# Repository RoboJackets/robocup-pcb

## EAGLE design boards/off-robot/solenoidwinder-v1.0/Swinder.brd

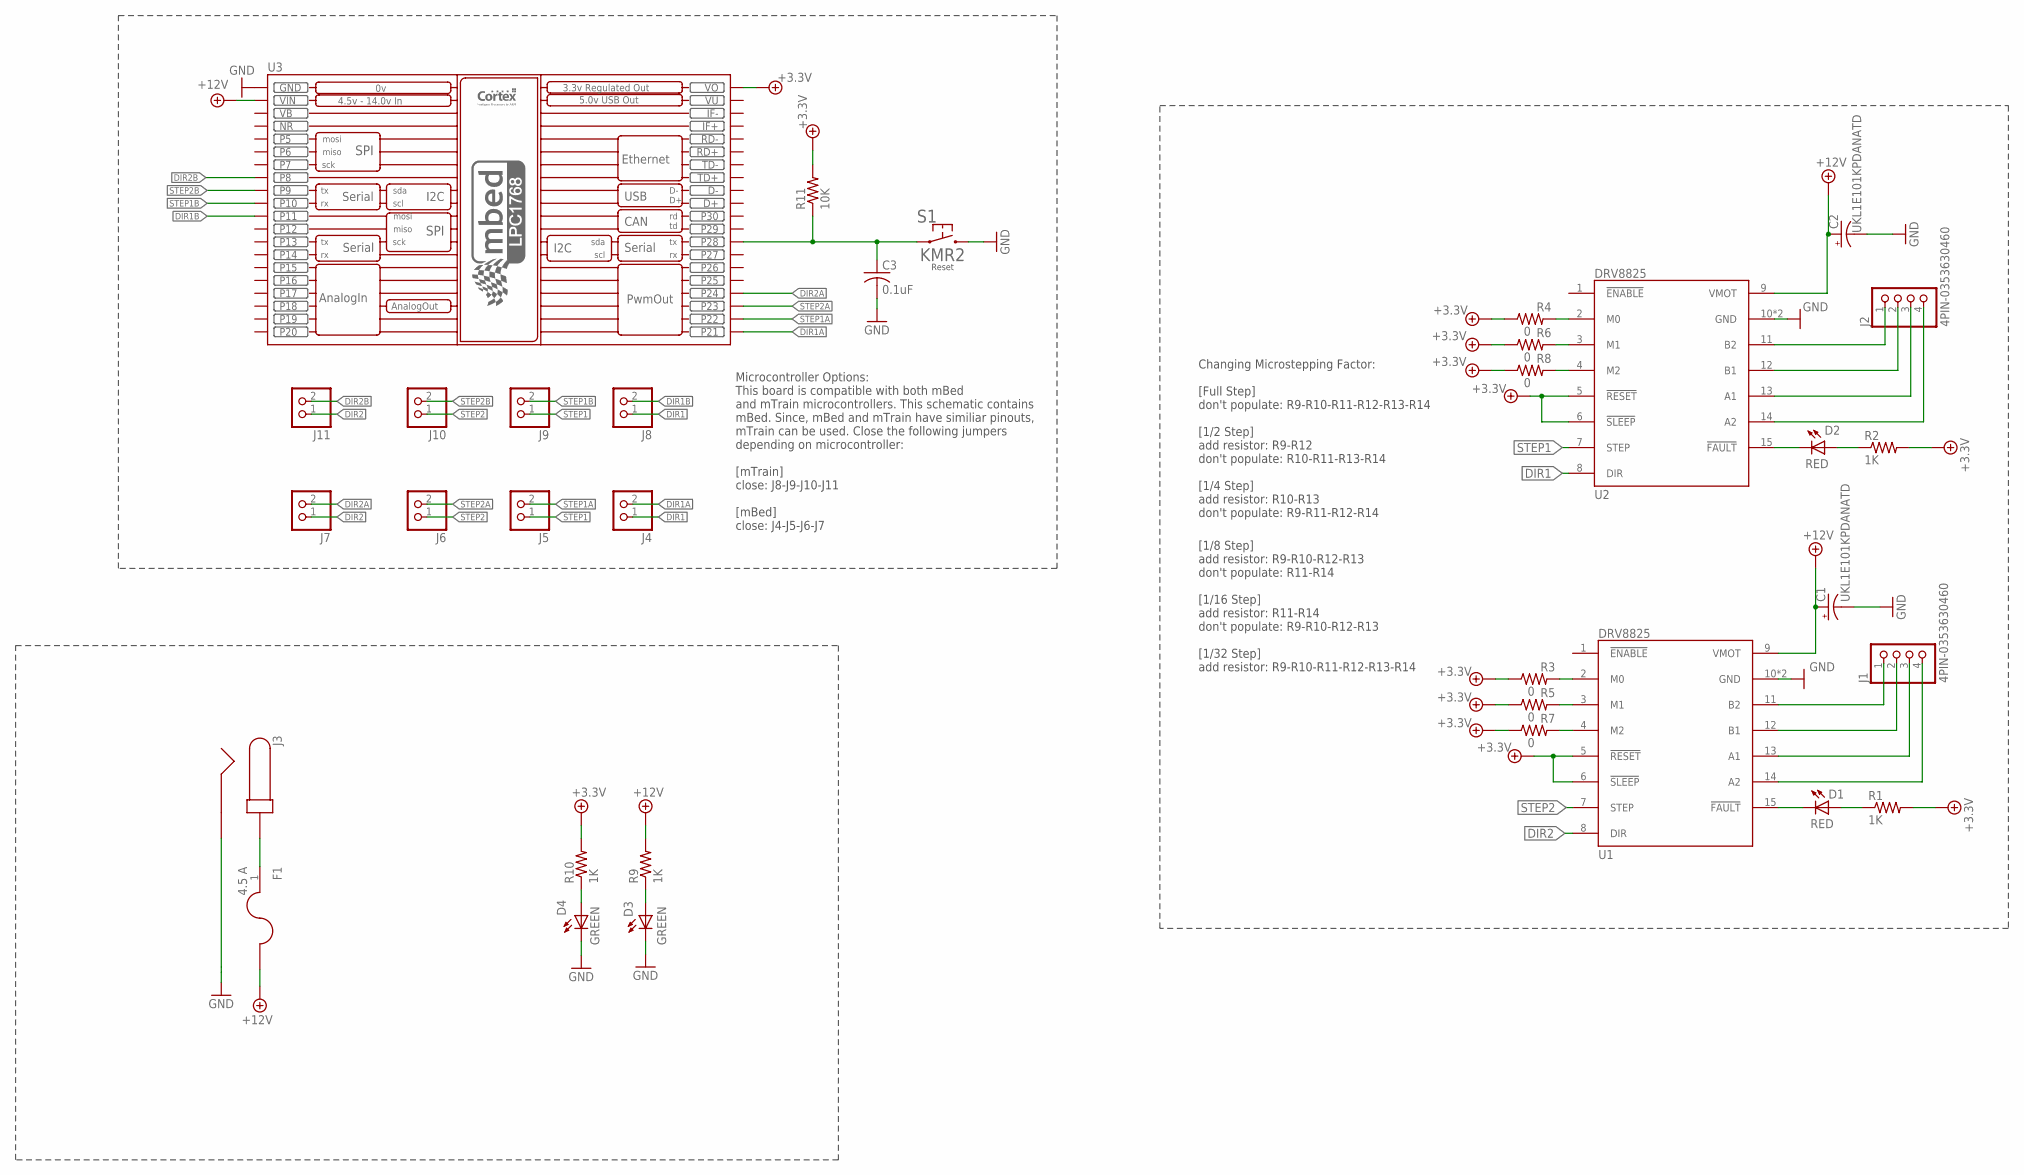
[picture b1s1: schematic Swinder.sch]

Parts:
C1, C2: UKL1E101KPDANATD
C3: 0.1uF; C0603
D1, D2: RED; CHIP-LED0603
D3, D4: GREEN; CHIP-LED0603
F1: 4.5 A; F1206
J1, J2: 4PIN-0353630460; 0353630460
J3: PJ-037A
J4, J5, J6, J7, J8, J9, J10, J11: CONN-2VERT; 1X2
R1, R2, R9, R10: 1K; R0603W
R3, R4, R5, R6, R7, R8: 0; R0603W
R11: 10K; R0603W
S1: KMR2
U1, U2: DRV8825
U3: MBED_NXP_LPC1768; MBED-KIT

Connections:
+3.3V: R1.2 (PIN2), R2.2 (PIN2), R3.1 (PIN1), R4.1 (PIN1), R5.1 (PIN1), R6.1 (PIN1), R7.1 (PIN1), R8.1 (PIN1), R10.2 (PIN2), R11.2 (PIN2), U1.5 (!RESET!), U1.6 (!SLEEP!), U2.5 (!RESET!), U2.6 (!SLEEP!), U3.VOUT (VO)
+12V: C1.+, C2.+, F1.2, R9.2 (PIN2), U1.9 (VMOT), U2.9 (VMOT), U3.VIN
A1$1: J2.3, U2.13 (A1)
A1$2: J1.3, U1.13 (A1)
A2$1: J2.4, U2.14 (A2)
A2$2: J1.4, U1.14 (A2)
B1$1: J2.2, U2.12 (B1)
B1$2: J1.2, U1.12 (B1)
B2$1: J2.1, U2.11 (B2)
B2$2: J1.1, U1.11 (B2)
DIR1: J4.1, J8.1, U2.8 (DIR)
DIR1A: J4.2, U3.P$21 (P21)
DIR1B: J8.2, U3.P$11 (P11)
DIR2: J7.1, J11.1, U1.8 (DIR)
DIR2A: J7.2, U3.P$24 (P24)
DIR2B: J11.2, U3.P$8 (P8)
FPOW: F1.1, J3.P$2 (1)
G1: D3.A, R9.1 (PIN1)
G2: D4.A, R10.1 (PIN1)
GND: C1.-, C2.-, C3.2, D3.C (K), D4.C (K), J3.P$1 (2), S1.2.1 (2), S1.2.2 (2), U1.10 (GND), U1.16 (GND), U2.10 (GND), U2.16 (GND), U3.GND
M0-1: R4.2 (PIN2), U2.2 (M0)
M0-2: R3.2 (PIN2), U1.2 (M0)
M1-1: R6.2 (PIN2), U2.3 (M1)
M1-2: R5.2 (PIN2), U1.3 (M1)
M2-1: R8.2 (PIN2), U2.4 (M2)
M2-2: R7.2 (PIN2), U1.4 (M2)
unnamed: C3.1, R11.1 (PIN1), S1.1.1 (1), S1.1.2 (1), U3.P$28 (P28)
R1-1: D2.A, R2.1 (PIN1)
R1-2: D2.C (K), U2.15 (!FAULT!)
R2-1: D1.A, R1.1 (PIN1)
R2-2: D1.C (K), U1.15 (!FAULT!)
STEP1: J5.1, J9.1, U2.7 (STEP)
STEP1A: J5.2, U3.P$22 (P22)
STEP1B: J9.2, U3.P$10 (P10)
STEP2: J6.1, J10.1, U1.7 (STEP)
STEP2A: J6.2, U3.P$23 (P23)
STEP2B: J10.2, U3.P$9 (P9)
VB: U3.VB
VU: U3.VU

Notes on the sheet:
Changing Microstepping Factor: [Full Step] don't populate: R9-R10-R11-R12-R13-R14 [1/2 Step] add resistor: R9-R12 don't populate: R10-R11-R13-R14 [1/4 Step] add resistor: R10-R13 don't populate: R9-R11-R12-R14
[1/8 Step] add resistor: R9-R10-R12-R13 don't populate: R11-R14 [1/16 Step] add resistor: R11-R14 don't populate: R9-R10-R12-R13 [1/32 Step] add resistor: R9-R10-R11-R12-R13-R14
Microcontroller Options: This board is compatible with both mBed and mTrain microcontrollers. This schematic contains mBed. Since, mBed and mTrain have similiar pinouts, mTrain can be used. Close the following jumpers depending on microcontroller: [mTrain] close: J8-J9-J10-J11 [mBed] close: J4-J5-J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

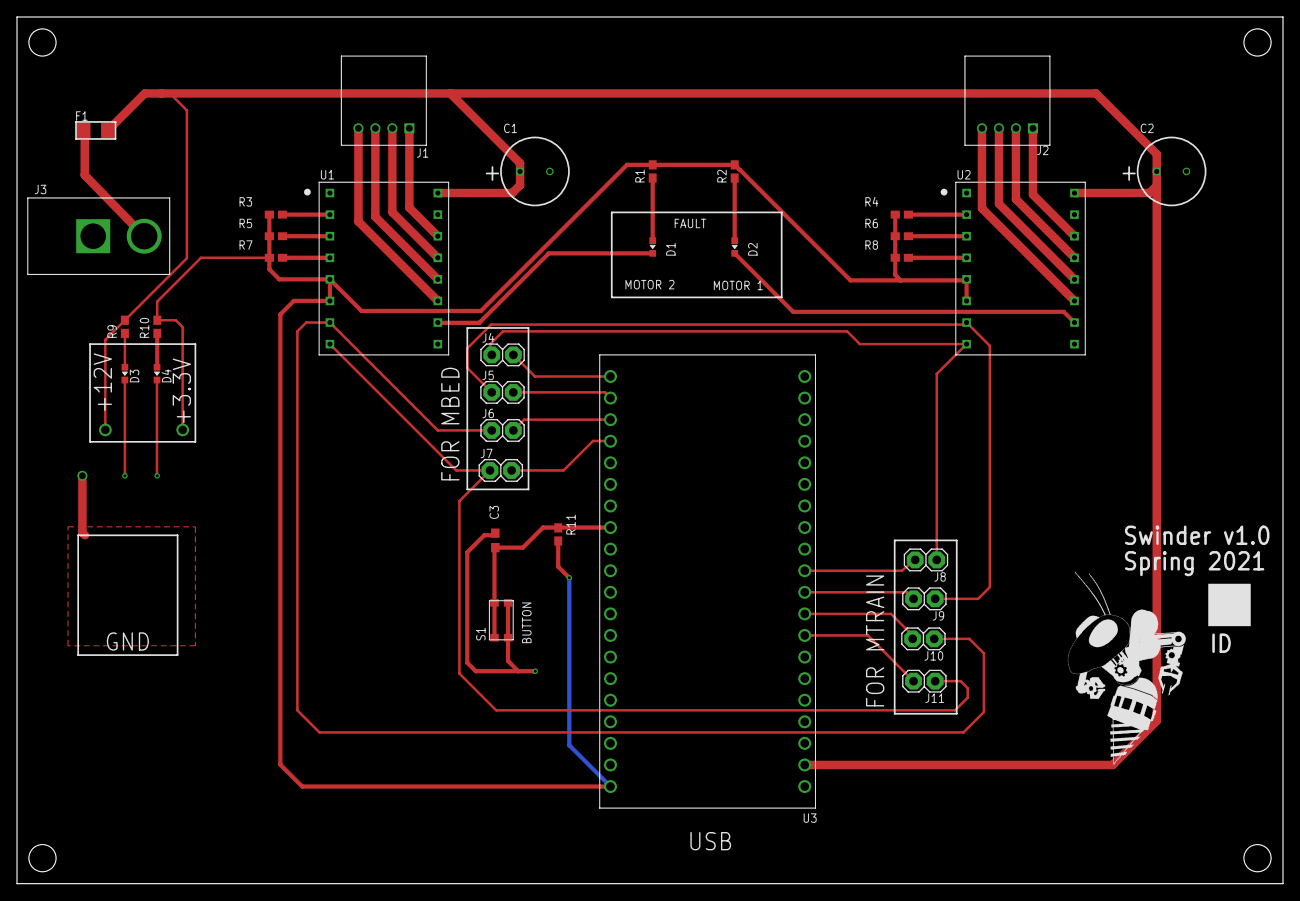
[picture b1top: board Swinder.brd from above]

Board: 2 copper layers, 149.0 x 102.0 mm, 35 parts (0 on the bottom side), 37 nets.

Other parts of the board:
U$1: ROBOBUZZ_1.2X

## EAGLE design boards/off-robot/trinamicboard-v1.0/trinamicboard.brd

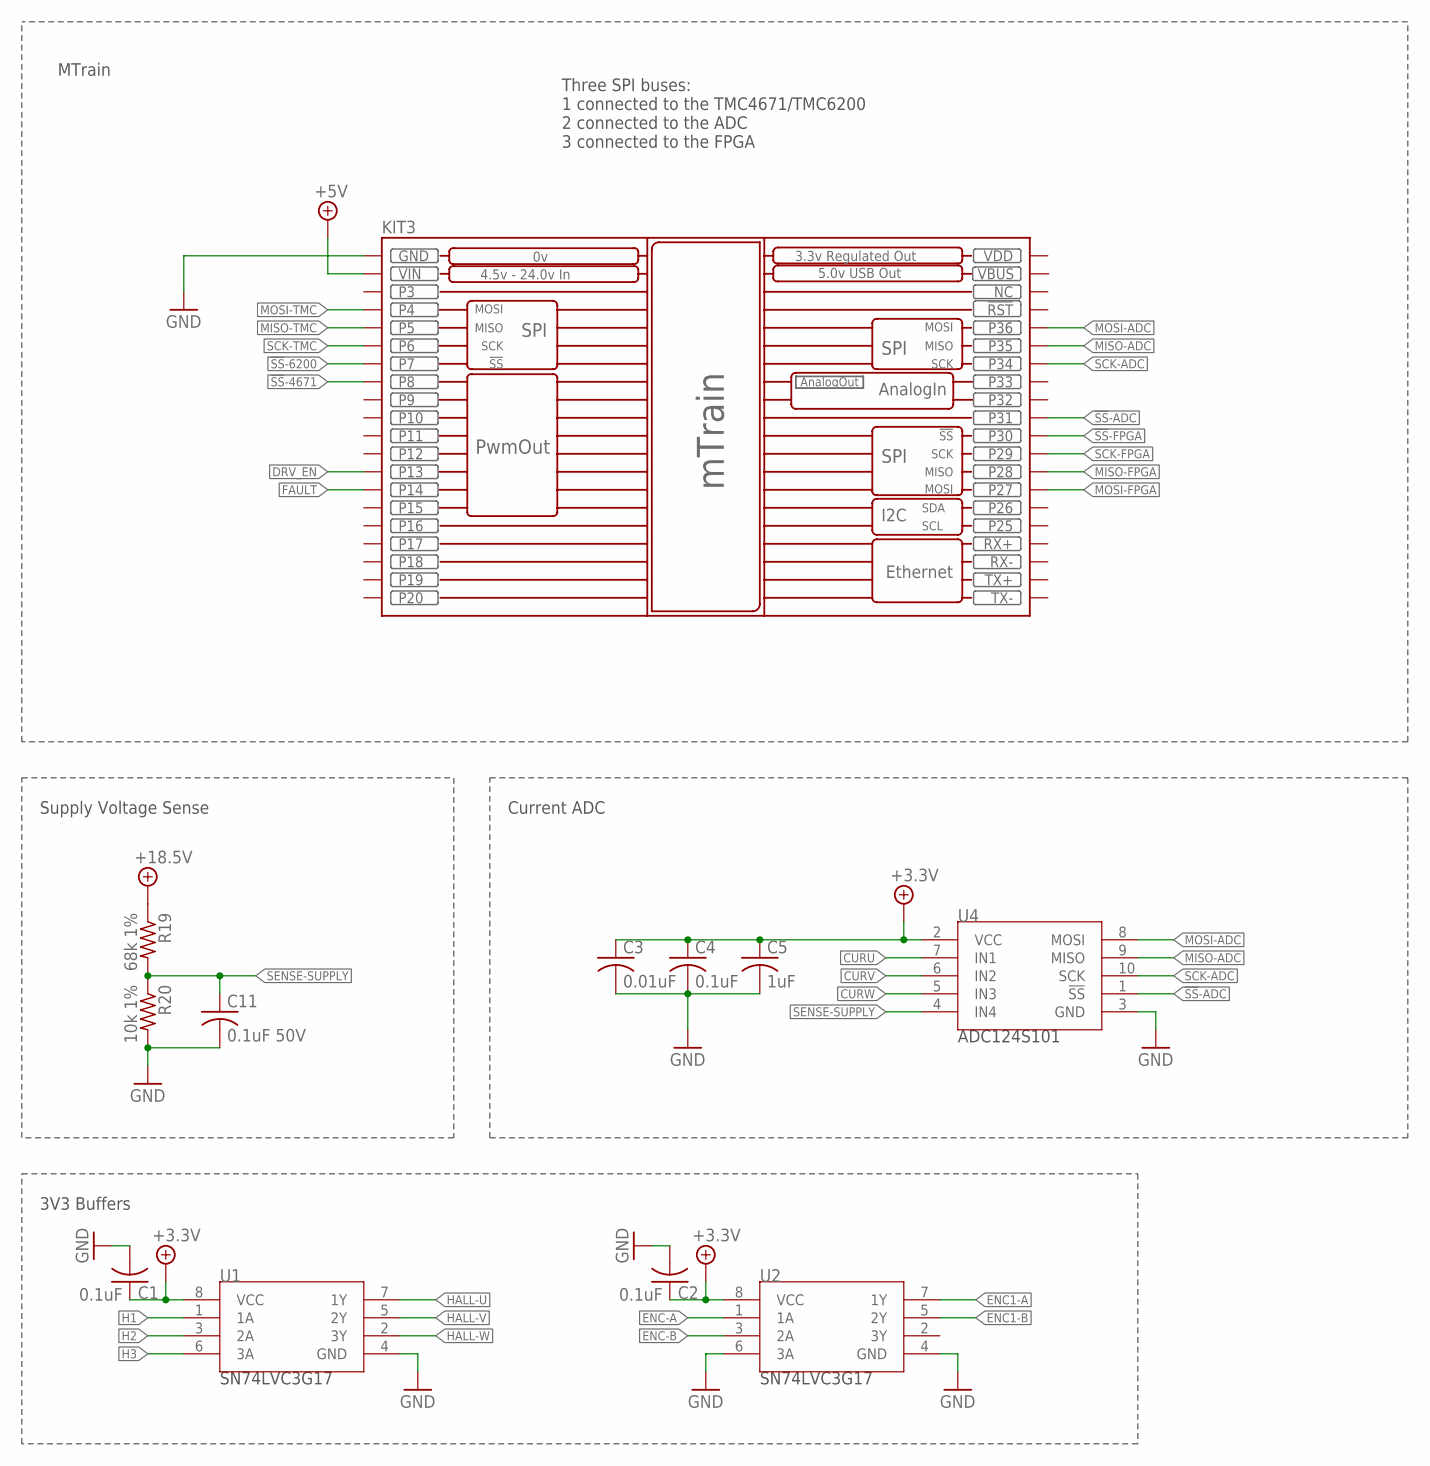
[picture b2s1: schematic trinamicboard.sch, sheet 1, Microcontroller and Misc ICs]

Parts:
C1, C2, C4: 0.1uF; C0603
C3: 0.01uF; C0603
C5: 1uF; C0603
C11: 0.1uF 50V; C0603
KIT3: MTRAIN; MTRAIN-KIT
R19: 68k 1%; R0603
R20: 10k 1%; R0603
U1, U2: SN74LVC3G17; VSSOP-8
U4: ADC124S101; VSSOP-10

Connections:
!SS!-4671: KIT3.P$8 (P8); also elsewhere on the board
!SS!-6200: KIT3.P$7 (P7); also elsewhere on the board
!SS!-ADC: KIT3.P$31 (P31), U4.1 (!SS); also elsewhere on the board
!SS!-FPGA: KIT3.P$30 (P30); also elsewhere on the board
+3.3V: C1.1, C2.1, C3.1, C4.1, C5.1, U1.8 (VCC), U2.8 (VCC), U4.2 (VCC); also elsewhere on the board
+5V: KIT3.VIN; also elsewhere on the board
+18.5V: R19.1; also elsewhere on the board
CURU: U4.7 (IN1); also elsewhere on the board
CURV: U4.6 (IN2); also elsewhere on the board
CURW: U4.5 (IN3); also elsewhere on the board
DRV_EN: KIT3.P$13 (P13); also elsewhere on the board
ENC1-A: U2.7 (1Y); also elsewhere on the board
ENC1-B: U2.5 (2Y); also elsewhere on the board
ENC-A: U2.1 (1A); also elsewhere on the board
ENC-B: U2.3 (2A); also elsewhere on the board
FAULT: KIT3.P$14 (P14); also elsewhere on the board
GND: C1.2, C2.2, C3.2, C4.2, C5.2, C11.2, KIT3.GND, R20.2, U1.4 (GND), U2.4 (GND), U2.6 (3A), U4.3 (GND); also elsewhere on the board
H1: U1.1 (1A); also elsewhere on the board
H2: U1.3 (2A); also elsewhere on the board
H3: U1.6 (3A); also elsewhere on the board
HALL-U: U1.7 (1Y); also elsewhere on the board
HALL-V: U1.5 (2Y); also elsewhere on the board
HALL-W: U1.2 (3Y); also elsewhere on the board
MISO-ADC: KIT3.P$35 (P35), U4.9 (MISO); also elsewhere on the board
MISO-FPGA: KIT3.P$28 (P28); also elsewhere on the board
MISO-TMC: KIT3.P$5 (P5); also elsewhere on the board
MOSI-ADC: KIT3.P$36 (P36), U4.8 (MOSI); also elsewhere on the board
MOSI-FPGA: KIT3.P$27 (P27); also elsewhere on the board
MOSI-TMC: KIT3.P$4 (P4); also elsewhere on the board
SCK-ADC: KIT3.P$34 (P34), U4.10 (SCK); also elsewhere on the board
SCK-FPGA: KIT3.P$29 (P29); also elsewhere on the board
SCK-TMC: KIT3.P$6 (P6); also elsewhere on the board
SENSE-SUPPLY: C11.1, R19.2, R20.1, U4.4 (IN4)
VBUS: KIT3.VBUS
VDD: KIT3.VDD

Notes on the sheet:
MTrain
Supply Voltage Sense
Three SPI buses: 1 connected to the TMC4671/TMC6200 2 connected to the ADC 3 connected to the FPGA
Current ADC
3V3 Buffers

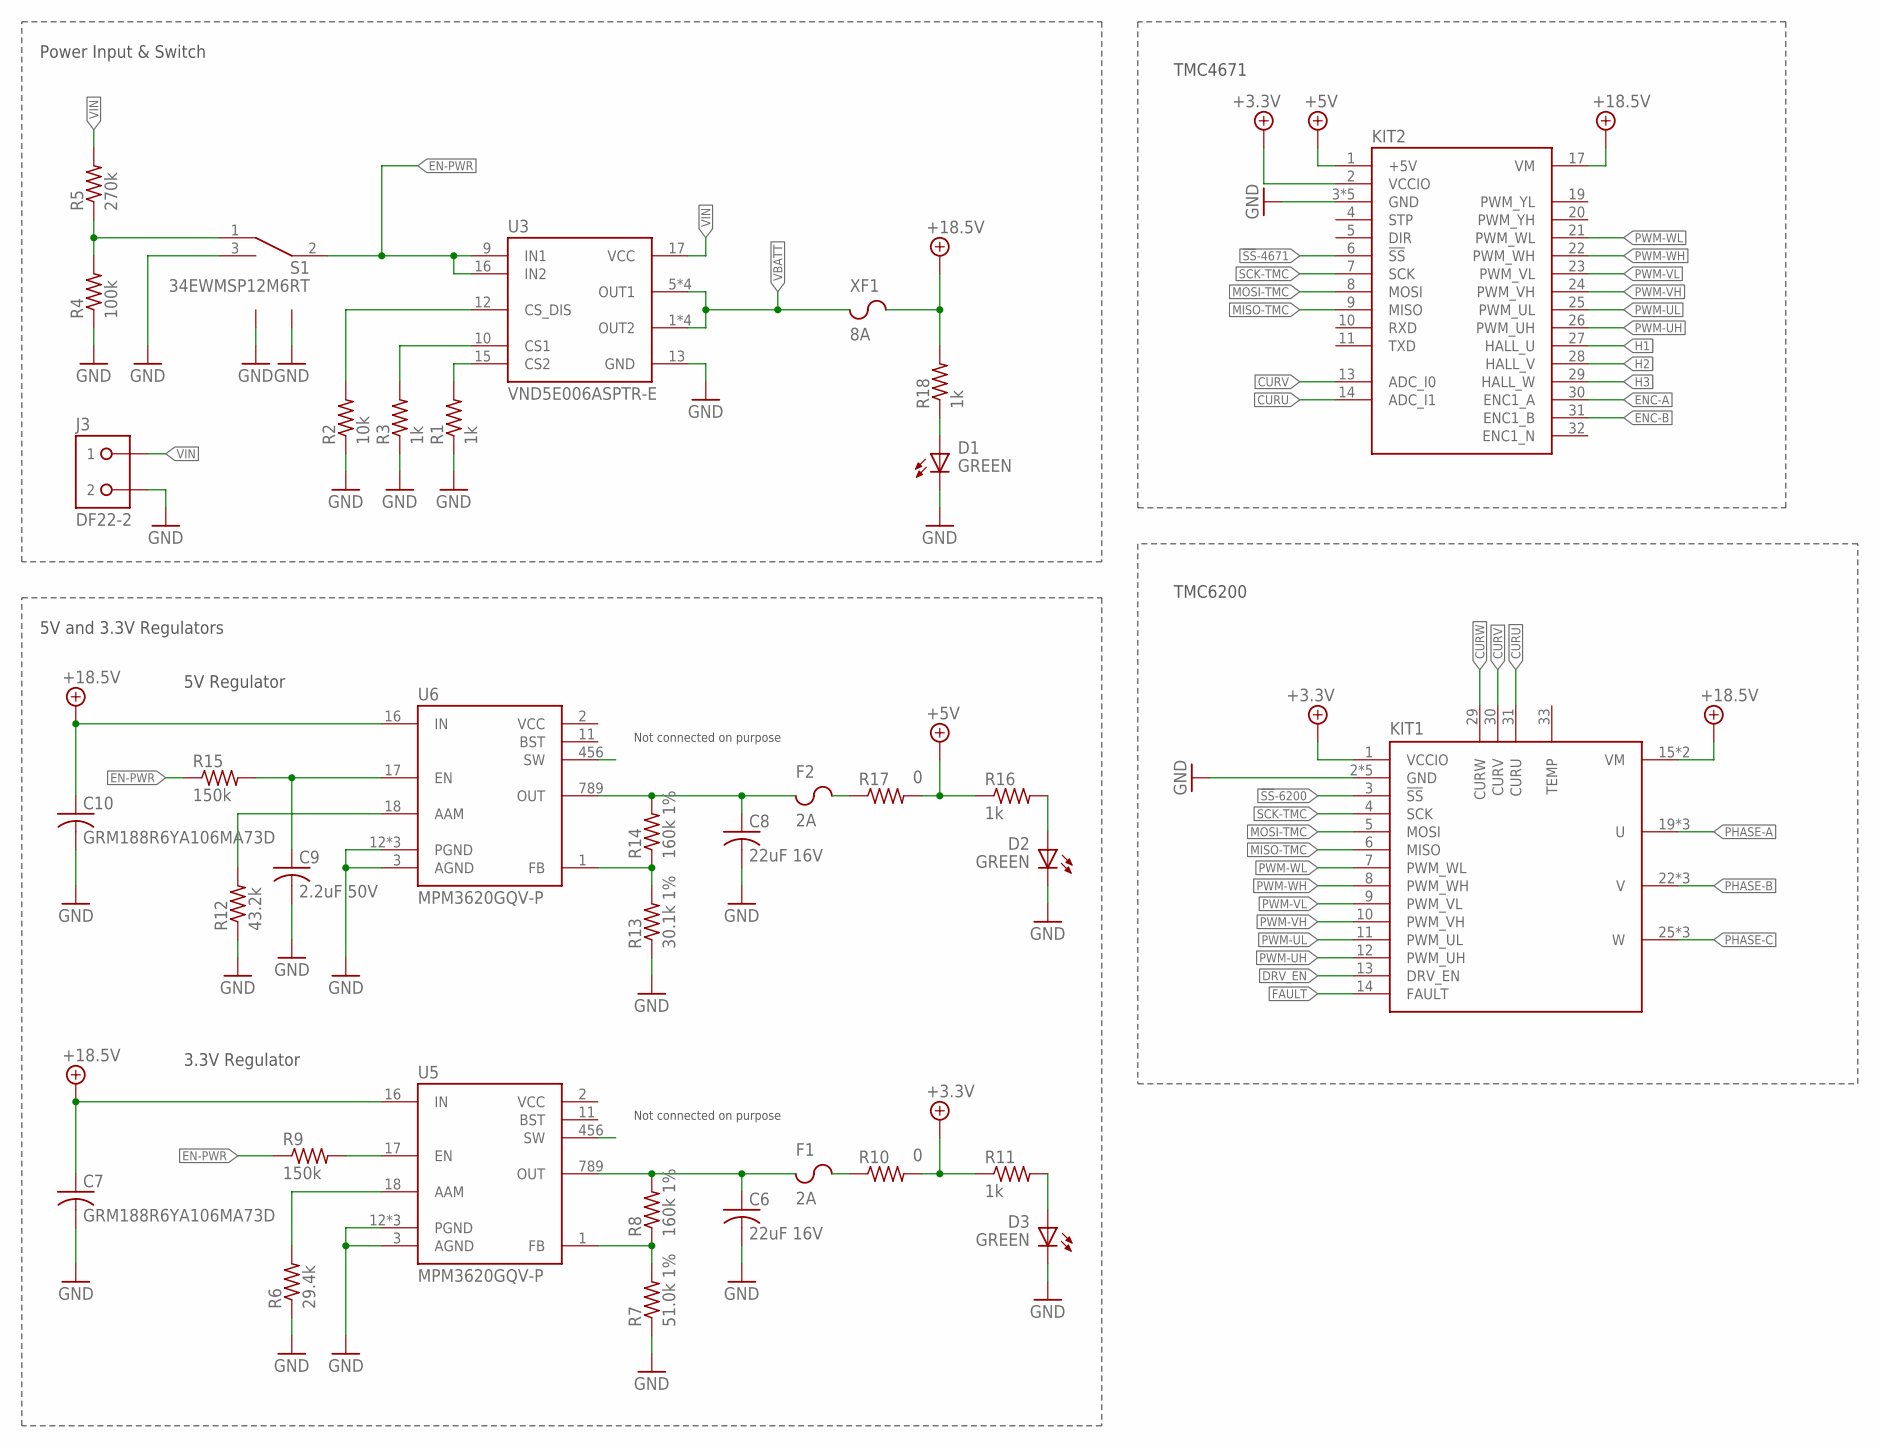
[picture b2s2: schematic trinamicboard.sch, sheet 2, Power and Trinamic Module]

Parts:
C6, C8: 22uF 16V; C0805
C7, C10: GRM188R6YA106MA73D; C0603
C9: 2.2uF 50V; C0603
D1, D2, D3: GREEN; CHIP-LED0603
F1, F2: 2A; FUSC2113X75
J3: DF22-2; DF22-2-H
KIT1: TMC6200-BOB
KIT2: TMC4671-BOB
R1, R3, R11, R16, R18: 1k; R0603
R2: 10k; R0603
R4: 100k; R0603
R5: 270k; R0603
R6: 29.4k; R0603
R7: 51.0k 1%; R0603
R8, R14: 160k 1%; R0603
R9, R15: 150k; R0603
R10, R17: 0; R0603
R12: 43.2k; R0603
R13: 30.1k 1%; R0603
S1: 34EWMSP12M6RT
U3: VND5E006ASPTR-E; POWERSO-16
U5, U6: MPM3620GQV-P; MPN MPM3620GQV-P; DIGIKEY 1589-1252-1-ND
XF1: 8A; 3557-2

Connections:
!SS!-4671: KIT2.6 (!SS!); also elsewhere on the board
!SS!-6200: KIT1.3 (!SS!); also elsewhere on the board
+3.3V: KIT1.1 (VCCIO), KIT2.2 (VCCIO), R10.2, R11.1; also elsewhere on the board
+3.3V-FUSE: C6.1, F1.1, R8.2, U5.789 (OUT)
+3.3V-LED: D3.A, R11.2
+3.3V-PREFUSE: F1.2, R10.1
+5V: KIT2.1 (+5V), R16.1, R17.2; also elsewhere on the board
+5V-FUSE: C8.1, F2.1, R14.2, U6.789 (OUT)
+5V-LED: D2.A, R16.2
+5V-PREFUSE: F2.2, R17.1
+18.5V: C7.1, C10.1, KIT1.15 (VM), KIT1.16 (VM), KIT2.17 (VM), R18.2, U5.16 (IN), U6.16 (IN), XF1.3 (2), XF1.4 (2); also elsewhere on the board
+18.5V-LED: D1.A, R18.1
AAM: R12.2, U6.18 (AAM)
AAM1: R6.2, U5.18 (AAM)
CS1: R3.2, U3.10 (CS1)
CS2: R1.2, U3.15 (CS2)
CS-DIS: R2.2, U3.12 (CS_DIS)
CURU: KIT1.31 (CURU), KIT2.14 (ADC_I1); also elsewhere on the board
CURV: KIT1.30 (CURV), KIT2.13 (ADC_I0); also elsewhere on the board
CURW: KIT1.29 (CURW); also elsewhere on the board
DRV_EN: KIT1.13 (DRV_EN); also elsewhere on the board
EN: C9.1, R15.2, U6.17 (EN)
EN1: R9.2, U5.17 (EN)
EN-PWR: R9.1, R15.1, S1.2 (COMMON), U3.9 (IN1), U3.16 (IN2)
EN-PWR-PRE: R4.2, R5.1, S1.1 (A)
ENC-A: KIT2.30 (ENC1_A); also elsewhere on the board
ENC-B: KIT2.31 (ENC1_B); also elsewhere on the board
FAULT: KIT1.14 (FAULT); also elsewhere on the board
FB: R13.2, R14.1, U6.1 (FB)
FB1: R7.2, R8.1, U5.1 (FB)
GND: C6.2, C7.2, C8.2, C9.2, C10.2, D1.C (K), D2.C (K), D3.C (K), J3.2, KIT1.2 (GND), KIT1.17 (GND), KIT1.18 (GND), KIT1.28 (GND), KIT1.32 (GND), KIT2.3 (GND), KIT2.12 (GND), KIT2.15 (GND), KIT2.16 (GND), KIT2.18 (GND), R1.1, R2.1, R3.1, R4.1, R6.1, R7.1, R12.1, R13.1, S1.3 (B), S1.LEG1, S1.LEG3 (LEG2), U3.13 (GND), U5.3 (AGND), U5.12 (PGND), U5.13 (PGND), U5.14 (PGND), U6.3 (AGND), U6.12 (PGND), U6.13 (PGND), U6.14 (PGND); also elsewhere on the board
H1: KIT2.27 (HALL_U); also elsewhere on the board
H2: KIT2.28 (HALL_V); also elsewhere on the board
H3: KIT2.29 (HALL_W); also elsewhere on the board
MISO-TMC: KIT1.6 (MISO), KIT2.9 (MISO); also elsewhere on the board
MOSI-TMC: KIT1.5 (MOSI), KIT2.8 (MOSI); also elsewhere on the board
PHASE-A: KIT1.19 (U), KIT1.20 (U), KIT1.21 (U); also elsewhere on the board
PHASE-B: KIT1.22 (V), KIT1.23 (V), KIT1.24 (V); also elsewhere on the board
PHASE-C: KIT1.25 (W), KIT1.26 (W), KIT1.27 (W); also elsewhere on the board
PWM-UH: KIT1.12 (PWM_UH), KIT2.26 (PWM_UH); also elsewhere on the board
PWM-UL: KIT1.11 (PWM_UL), KIT2.25 (PWM_UL); also elsewhere on the board
PWM-VH: KIT1.10 (PWM_VH), KIT2.24 (PWM_VH); also elsewhere on the board
PWM-VL: KIT1.9 (PWM_VL), KIT2.23 (PWM_VL); also elsewhere on the board
PWM-WH: KIT1.8 (PWM_WH), KIT2.22 (PWM_WH); also elsewhere on the board
PWM-WL: KIT1.7 (PWM_WL), KIT2.21 (PWM_WL); also elsewhere on the board
SCK-TMC: KIT1.4 (SCK), KIT2.7 (SCK); also elsewhere on the board
SW: U6.456 (SW)
SW1: U5.456 (SW)
VBATT: U3.1 (OUT2), U3.2 (OUT2), U3.3 (OUT2), U3.4 (OUT2), U3.5 (OUT1), U3.6 (OUT1), U3.7 (OUT1), U3.8 (OUT1), XF1.1, XF1.2 (1)
VIN: J3.1, R5.2, U3.17 (VCC)

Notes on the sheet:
Power Input & Switch
5V and 3.3V Regulators
Not connected on purpose
5V Regulator
3.3V Regulator
TMC4671
TMC6200

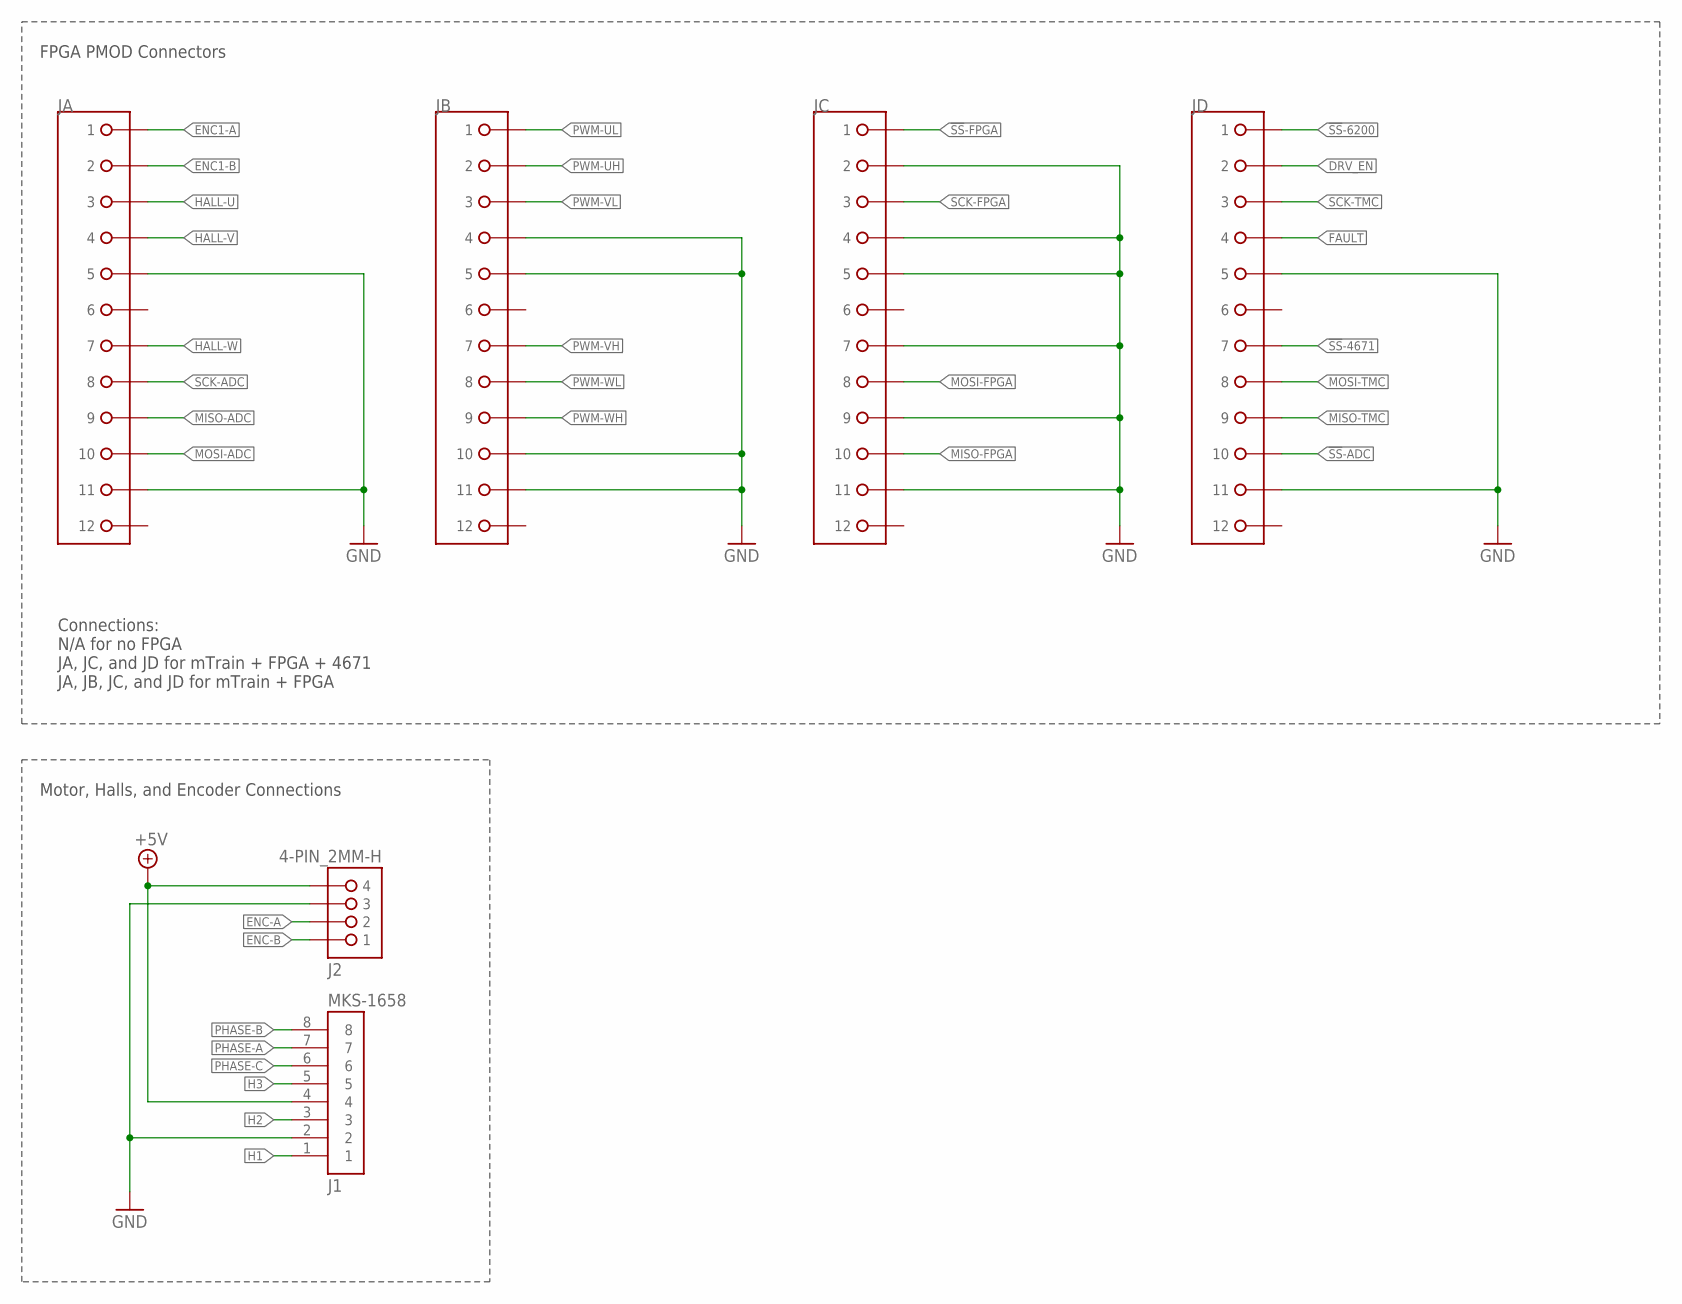
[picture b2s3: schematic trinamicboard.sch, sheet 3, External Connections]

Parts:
J1: MKS-1658
J2: 4-PIN_2MM-H; 2MM-4-H
JA: PMOD
JB: PMOD
JC: PMOD
JD: PMOD

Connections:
!SS!-4671: JD.1 (7); also elsewhere on the board
!SS!-6200: JD.7 (1); also elsewhere on the board
!SS!-ADC: JD.4 (10); also elsewhere on the board
!SS!-FPGA: JC.7 (1); also elsewhere on the board
+5V: J1.4, J2.4; also elsewhere on the board
DRV_EN: JD.8 (2); also elsewhere on the board
ENC1-A: JA.7 (1); also elsewhere on the board
ENC1-B: JA.8 (2); also elsewhere on the board
ENC-A: J2.2; also elsewhere on the board
ENC-B: J2.1; also elsewhere on the board
FAULT: JD.10 (4); also elsewhere on the board
GND: J1.2, J2.3, JA.5 (11), JA.11 (5), JB.4 (10), JB.5 (11), JB.10 (4), JB.11 (5), JC.1 (7), JC.3 (9), JC.5 (11), JC.8 (2), JC.10 (4), JC.11 (5), JD.5 (11), JD.11 (5); also elsewhere on the board
H1: J1.1; also elsewhere on the board
H2: J1.3; also elsewhere on the board
H3: J1.5; also elsewhere on the board
HALL-U: JA.9 (3); also elsewhere on the board
HALL-V: JA.10 (4); also elsewhere on the board
HALL-W: JA.1 (7); also elsewhere on the board
MISO-ADC: JA.3 (9); also elsewhere on the board
MISO-FPGA: JC.4 (10); also elsewhere on the board
MISO-TMC: JD.3 (9); also elsewhere on the board
MOSI-ADC: JA.4 (10); also elsewhere on the board
MOSI-FPGA: JC.2 (8); also elsewhere on the board
MOSI-TMC: JD.2 (8); also elsewhere on the board
PHASE-A: J1.7; also elsewhere on the board
PHASE-B: J1.8; also elsewhere on the board
PHASE-C: J1.6; also elsewhere on the board
PWM-UH: JB.8 (2); also elsewhere on the board
PWM-UL: JB.7 (1); also elsewhere on the board
PWM-VH: JB.1 (7); also elsewhere on the board
PWM-VL: JB.9 (3); also elsewhere on the board
PWM-WH: JB.3 (9); also elsewhere on the board
PWM-WL: JB.2 (8); also elsewhere on the board
SCK-ADC: JA.2 (8); also elsewhere on the board
SCK-FPGA: JC.9 (3); also elsewhere on the board
SCK-TMC: JD.9 (3); also elsewhere on the board

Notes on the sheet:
Motor, Halls, and Encoder Connections
FPGA PMOD Connectors
Connections: N/A for no FPGA JA, JC, and JD for mTrain + FPGA + 4671 JA, JB, JC, and JD for mTrain + FPGA

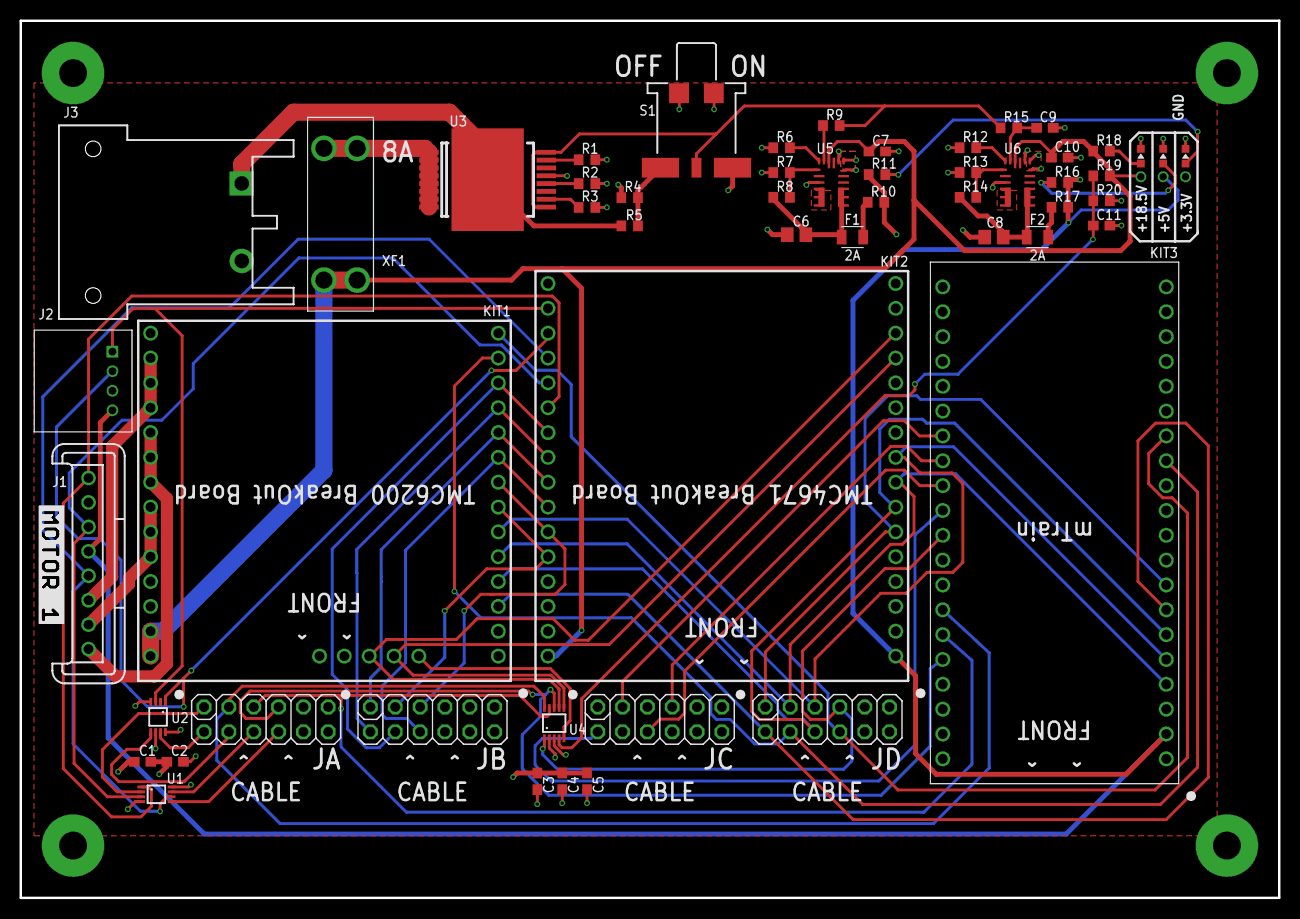
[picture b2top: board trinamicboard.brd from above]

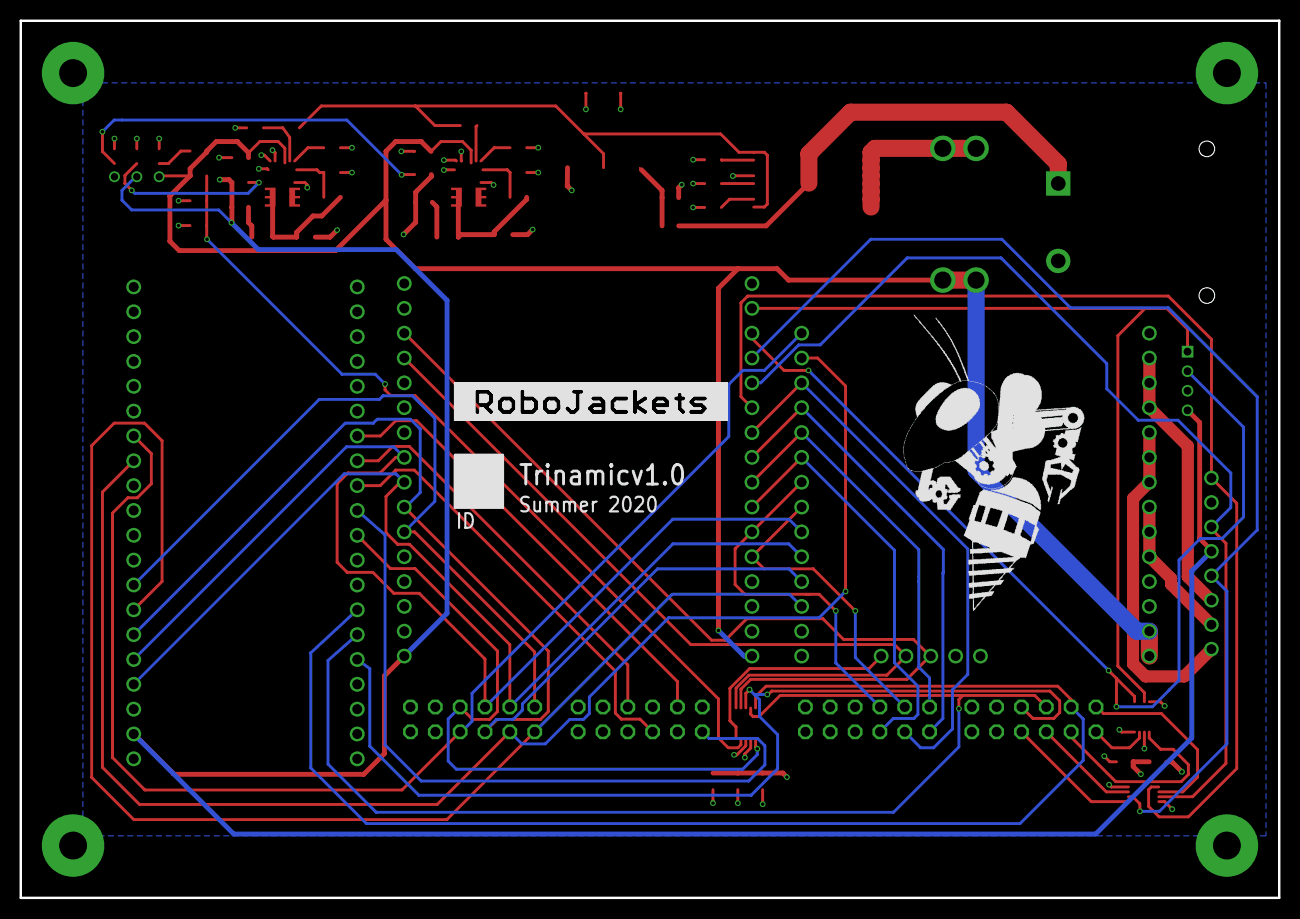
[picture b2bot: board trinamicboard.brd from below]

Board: 4 copper layers, 128.7 x 89.7 mm, 57 parts (2 on the bottom side), 62 nets.

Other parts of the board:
U$1: MOTOR-1
U$2: ROBOBUZZ_1.4X
U$100: ROBOJACKETS

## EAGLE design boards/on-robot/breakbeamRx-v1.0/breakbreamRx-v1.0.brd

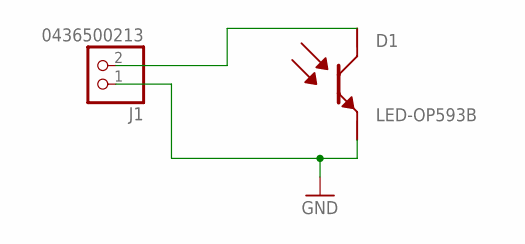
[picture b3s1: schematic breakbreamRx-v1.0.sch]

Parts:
D1: LED-OP593B; OP593B
J1: 0436500213

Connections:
GND: D1.P$1 (C), J1.1
RX: D1.P$2 (E), J1.2

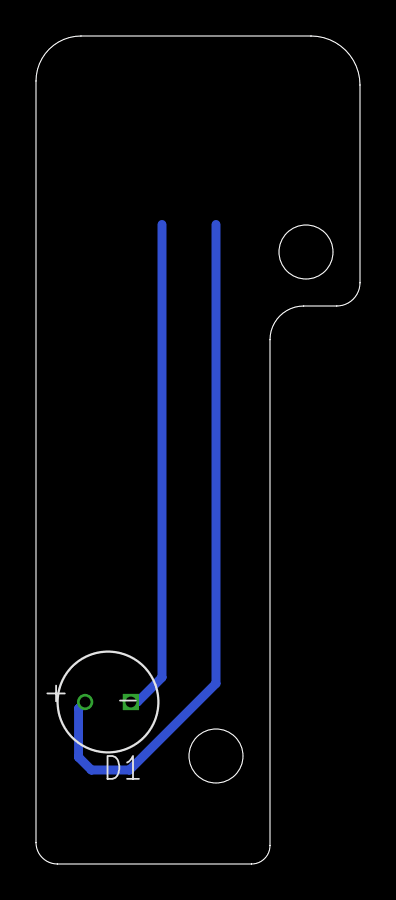
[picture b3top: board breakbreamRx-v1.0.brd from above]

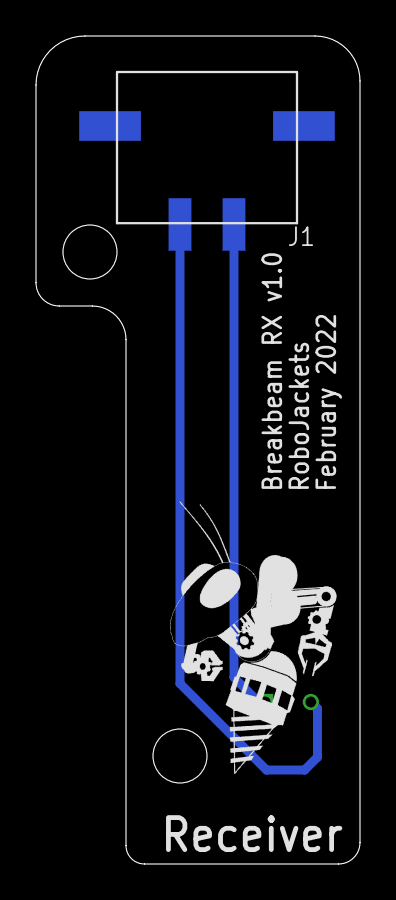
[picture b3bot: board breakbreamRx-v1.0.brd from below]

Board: 2 copper layers, 18.0 x 46.0 mm, 3 parts (2 on the bottom side), 2 nets.

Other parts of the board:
U$1: ROBOBUZZ_0.8X

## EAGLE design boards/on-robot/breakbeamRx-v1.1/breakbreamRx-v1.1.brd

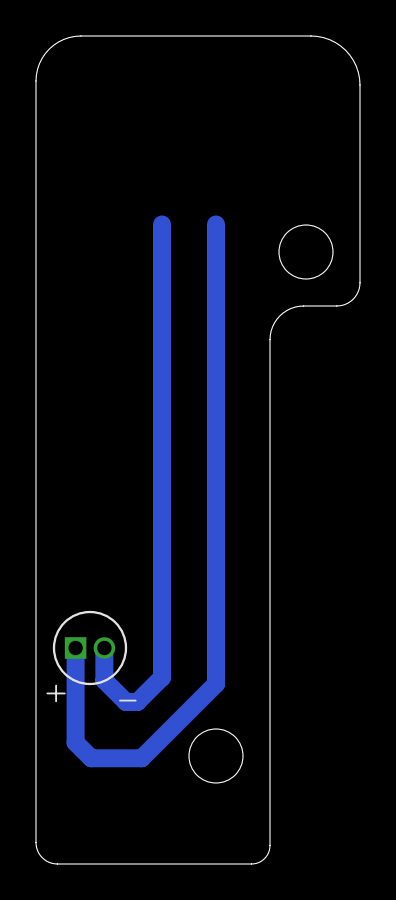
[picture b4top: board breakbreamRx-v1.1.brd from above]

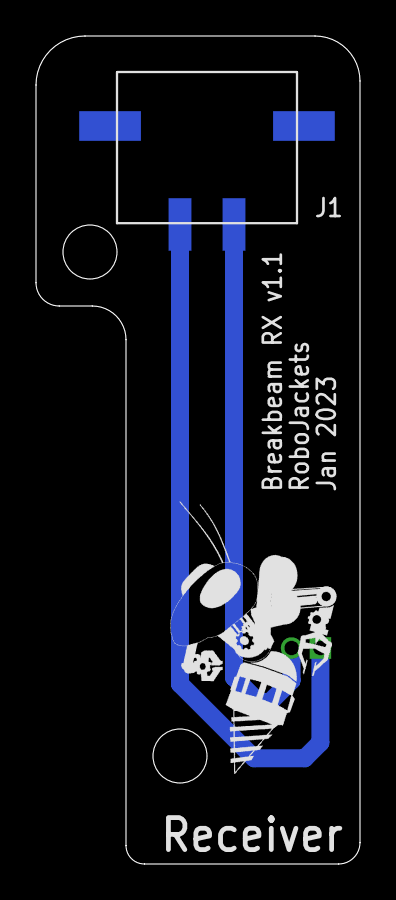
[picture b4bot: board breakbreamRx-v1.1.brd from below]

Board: 2 copper layers, 18.0 x 46.0 mm, 3 parts (2 on the bottom side), 2 nets.

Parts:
J1: 0436500213
Q1: LTR-209
U$1: ROBOBUZZ_0.8X

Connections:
GND: J1.1, Q1.P$1
RX: J1.2, Q1.P$2

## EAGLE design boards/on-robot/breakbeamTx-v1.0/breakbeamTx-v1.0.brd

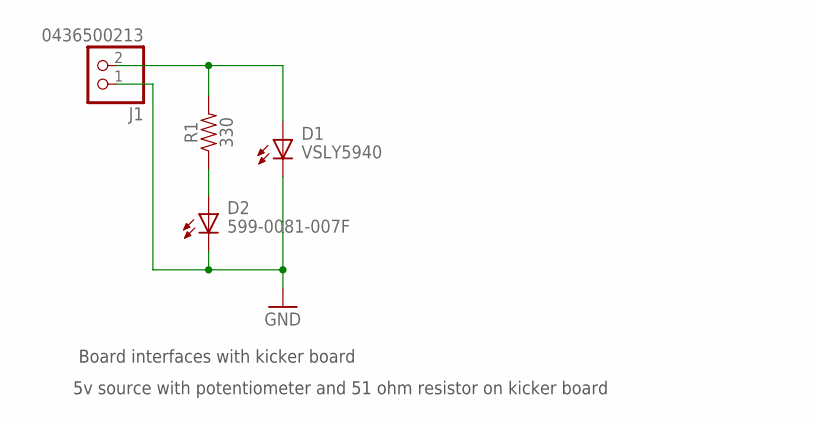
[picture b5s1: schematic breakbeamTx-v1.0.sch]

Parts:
D1: VSLY5940
D2: 599-0081-007F; 599-0081-007F_DIA
J1: 0436500213
R1: 330; 0603

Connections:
BB_TX: D1.A, J1.2, R1.2
GND: D1.K, D2.2 (K), J1.1
unnamed: D2.1 (A), R1.1

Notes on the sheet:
Board interfaces with kicker board
5v source with potentiometer and 51 ohm resistor on kicker board

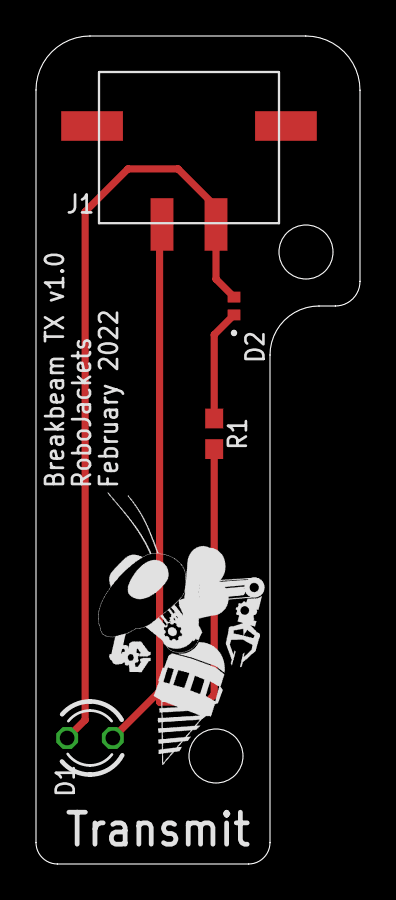
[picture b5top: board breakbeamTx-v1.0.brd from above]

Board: 2 copper layers, 18.0 x 46.0 mm, 5 parts (0 on the bottom side), 3 nets.

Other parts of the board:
U$1: ROBOBUZZ_0.8X

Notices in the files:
parts and their libraries:
COPYRIGHT: Copyright (C) 2023 Ultra Librarian. All rights reserved.
COPYRIGHT: Copyright (C) 2022 Ultra Librarian. All rights reserved.
